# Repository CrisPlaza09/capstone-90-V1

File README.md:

# PCB_esp — Holter (Grupo 11, IEE2913)

Proyecto KiCad 10 de la placa del ESP32 (avance 90 %). Abrir `PCB_esp.kicad_pro`.

> Requiere **KiCad 10**: los archivos están guardados en formato 10 y versiones anteriores no los abren.

Las librerías propias vienen dentro del repo (`libs/`) y se cargan con `${KIPRJMOD}`
(tablas `sym-lib-table` y `fp-lib-table` del proyecto), así que no hay que configurar
nada. El ESP32-S2-WROVER usa la librería estándar `RF_Module` y su modelo 3D usa
`${KICAD10_3DMODEL_DIR}`, que KiCad 10 instala por defecto.

## Componentes

| Ref | Componente | Símbolo | Footprint |
|-----|------------|---------|-----------|
| U1 | ESP32-S2-WROVER | `RF_Module` (estándar) | `RF_Module` (estándar) |
| U2 | AD8232 (SparkFun SEN-12650) | `SEN-12650` | `SEN-12650` |
| U3 | HX711 (módulo) | `HX711_Module` | `HX711_Module` |
| U4 | Sensor de presión MPS20N0040D | `MPS20N0040D` | `MPS20N0040D` |
| U5 | OLED 0,96" DM-OLED096-636 | `DM-OLED096-636` | `DM-OLED096-636` |
| U6 | Módulo microSD mini | `MicroSD_Mini_Module` | `MicroSD_Mini_KiCad` |

## Estructura

- `libs/symbols/` símbolos propios (`.kicad_sym`)
- `libs/footprints/` footprints propios (`.pretty`)
- `libs/3d/` modelos 3D propios (el `.step` del OLED se enlaza con `${KIPRJMOD}`)

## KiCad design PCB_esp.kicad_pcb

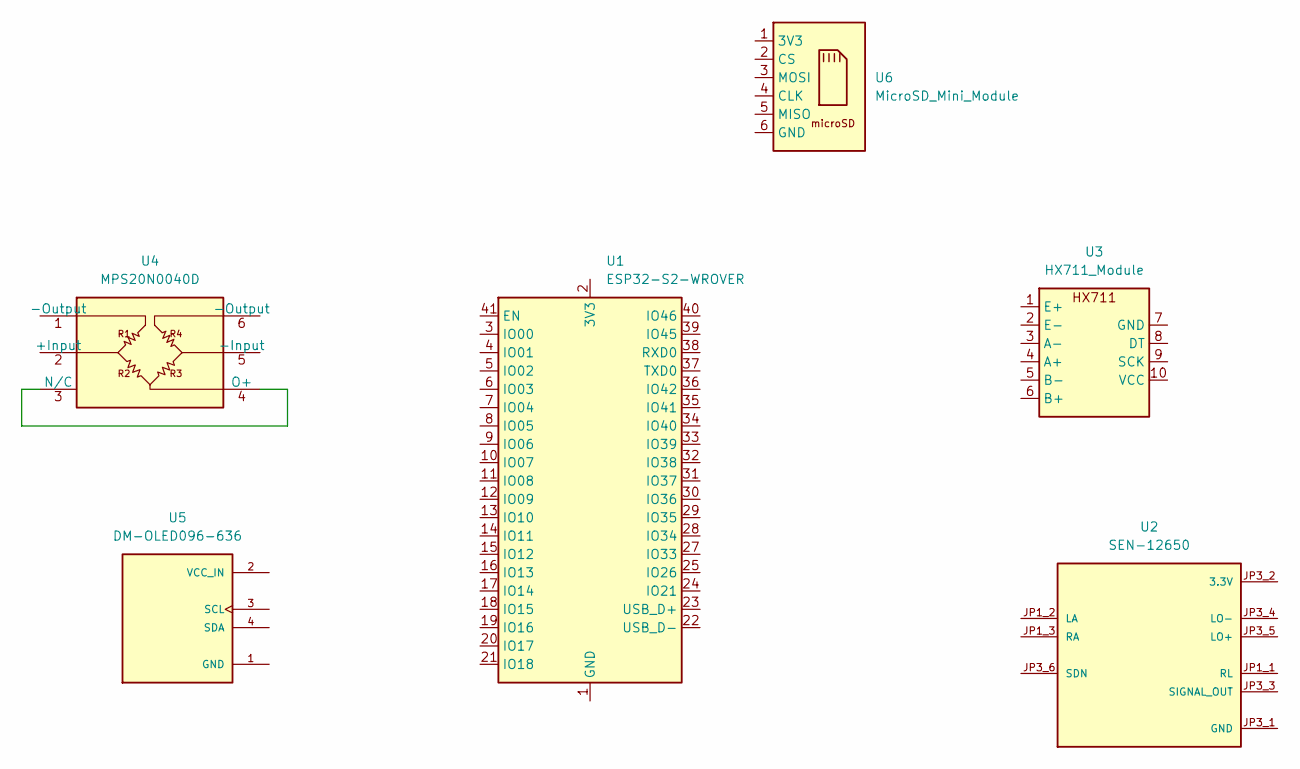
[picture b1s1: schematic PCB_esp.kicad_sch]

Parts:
U1: ESP32-S2-WROVER
U2: SEN-12650; MODULE_SEN-12650; MPN SEN-12650
U3: HX711_Module
U4: MPS20N0040D; MPS20N0040D_2x03_P2.54mm_W10.16mm
U5: DM-OLED096-636; MODULE_DM-OLED096-636; MPN DM-OLED096-636
U6: MicroSD_Mini_Module; MicroSD_Mini_Module_1x06_P2.54mm

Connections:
unnamed: U1.1 (GND), U1.26 (GND), U1.42 (GND), U1.43 (GND)
unnamed: U4.3 (N/C), U4.4 (O+)

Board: 2 copper layers, 6 parts (0 on the bottom side), 2 nets, no tracks yet.
